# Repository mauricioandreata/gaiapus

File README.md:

# Gaiapus · Field Shift

**NASA Space Apps Challenge 2026** · Challenge *Field Shift: Adapting Farms with NASA Data* · Team Gaiapus

Gaiapus helps farmers decide **what to plant next, and when**, without leaving the soil bare between one crop and the next. Recommendations start from open NASA data, which covers any place on the planet. Where local precision matters, a **low-cost solar soil stake** measures the field and corrects the satellite data for that spot.

> The tool suggests and explains; the final decision always belongs to the farmer and the local agronomist.

| 3D model of the stake (real design, generated from the boards and the case) | Product concept (illustrative image, **AI-generated**) |
|---|---|
|  |  |

*Portuguese version: [`README.pt-BR.md`](README.pt-BR.md).*

---

## The problem

- Satellite data is the only source available to most farmers, but it is **too coarse to decide on a single field**: SMAP soil moisture comes in 9 km cells, GPM IMERG rainfall in ~10 km cells, and no satellite measures soil temperature at 15 or 40 cm.
- Commercial soil sensors cost **hundreds of dollars per depth**, plus a datalogger. They are out of reach for the farmers who most need guidance.
- Worldwide, more than 500 million family farms produce about 80 % of the world's food by value (FAO), and agriculture accounts for about 72 % of all freshwater withdrawals (FAO, AQUASTAT 2025).
- **(Brazil, pilot region)** 77 % of rural establishments are family farms and only about 20 % receive technical assistance (IBGE, Agricultural Census 2017).

## The solution in three tiers

| Tier | For whom | What goes to the field | How the farmer receives it |
|---|---|---|---|
| **0 · Satellite** | any farmer, zero cost | nothing, just the location | app and WhatsApp (voice and text) |
| **1 · Stake** | small farms | 1 solar stake + 1 community gateway (cooperative, extension service) | WhatsApp + green/yellow/red LEDs on the stake |
| **2 · Network** | medium and large farms | several stakes per management zone | app, per field |

```mermaid
flowchart LR
    NASA["NASA data<br/>POWER · GPM IMERG · SMAP<br/>HLS · SRTM"] --> M["Decision engine<br/>rotation and planting window"]
    E["Gaiapus stake<br/>soil moisture and temp. 15/40 cm<br/>air · rain"] -- "LoRa" --> G["Community<br/>gateway"]
    G -- "Wi-Fi / MQTT" --> M
    M --> P["Farmer<br/>WhatsApp · app · stake LEDs"]
```

---

## What is in this repository

This repository contains the **device**: hardware, firmware and mechanics. The app and the decision engine with the NASA data live in the software team's repository. The two connect through the data contract in [`docs/protocolo-dados.md`](docs/protocolo-dados.md) (Portuguese).

### Current status
| Part | Status | Evidence |
|---|---|---|
| Schematics of both boards (head + probe) | complete, ERC with no errors | `hardware/gaiapus-node`, `hardware/gaiapus-probe` |
| Head PCB (90 × 50 mm, 4 layers) | routed 51/51 nets, DRC with no errors | `hardware/gaiapus-node/*.kicad_pcb`, 3D model `.glb`/`.step` |
| Probe PCB (22 × 450 mm, 2 layers) | routed 12/12 nets, DRC with no errors | `hardware/gaiapus-probe/*.kicad_pcb` |
| Bill of materials with cost | every main part with LCSC code and price | `bom/bom_custos_BRL.xlsx` |
| Power budget | computed from datasheet values | `power/power_budget.py` |
| Case, stake and rain gauge (rev G) | drawings, printable 3MF files, full 3D assembly, 36/36 checks passed, 0 mm³ interference | `mechanical/` |
| Stake and gateway firmware | complete, tested on a PC (9 simulated hours, network outage, resend) | `firmware/` |
| Bench prototype | dev-board ESP32 + off-the-shelf sensors, same firmware and protocol | `firmware/src/main.cpp` |
| Physical PCB prototype | **not manufactured yet** | — |

### Key numbers
| | Value |
|---|---|
| Measurements | soil moisture and temperature at 15 and 40 cm, air temperature and humidity, rainfall, battery |
| Radio | LoRa (SX1262), configurable regional band 868/915 MHz; 25 bytes every 30 min |
| Consumption | 1.2–1.8 mAh/day (50–75 µA average) |
| Energy | 0.3 W panel (68 × 37 mm) + LiFePO4 18650 cell; positive balance even on a cloudy day |
| Autonomy without sun | about 1 year by calculation (target was 14 days) |
| Rain gauge | tipping bucket, 100 mm collector, 0.201 mm per pulse |
| Component cost | ≈ US$ 30 per stake (1 unit), less in volume; PCB, assembly and case still to be quoted |
| Comparison | a commercial single-depth sensor costs US$ 258–615, without the logger |

Details, sources and limits of each number: [`docs/hardware.md`](docs/hardware.md).

---

## Where to start

### Judges and reviewers
1. [`docs/hardware.md`](docs/hardware.md): why each component, power, cost, market comparison, risks.
2. [`docs/firmware.md`](docs/firmware.md): how the stake measures, stores and sends data all the way to the app.
3. [`docs/protocolo-dados.md`](docs/protocolo-dados.md) (Portuguese): the 25-byte packet and the JSON the app receives.
4. 3D model of the whole stake: [`mechanical/cad/revG/gaiapus-stake-revG-assembly.glb`](mechanical/cad/revG/gaiapus-stake-revG-assembly.glb) (opens in Windows 3D Viewer, Blender or https://gltf-viewer.donmccurdy.com).
5. Case and rain-gauge drawings: [`mechanical/drawings/gaiapus-case-revG.pdf`](mechanical/drawings/gaiapus-case-revG.pdf); exploded view: [`mechanical/cad/revG/renders/exploded-revG.png`](mechanical/cad/revG/renders/exploded-revG.png).
6. Design decisions and their reasons: [`docs/decisoes.md`](docs/decisoes.md) (Portuguese).

### Team
| I want to... | Do |
|---|---|
| Open the boards | KiCad 8: `hardware/gaiapus-node/gaiapus-node.kicad_pro` and `hardware/gaiapus-probe/gaiapus-probe.kicad_pro` |
| Change the circuit | edit `hardware/tools/gen_kicad.py` and run `check_kicad.py` (see [`hardware/README.md`](hardware/README.md)); close KiCad first |
| Flash the stake | `cd firmware && pio run -e stake-lora -t upload` (other targets in [`firmware/README.md`](firmware/README.md)) |
| Run the firmware tests | in `firmware/test`, commands in [`firmware/README.md`](firmware/README.md) (needs only `gcc` and `python3`) |
| Recompute the energy budget | `python power/power_budget.py --help` |
| Integrate the app | subscribe to `gaiapus/devices/+/up` and publish the command to `gaiapus/devices/{id}/down` ([`docs/protocolo-dados.md`](docs/protocolo-dados.md)) |

---

## Structure

| Folder | Contents |
|---|---|
| `docs/` | documentation: hardware, firmware, protocol, requirements, decisions |
| `hardware/gaiapus-node/` | head board (KiCad 8): ESP32-S3, LoRa radio, solar power, air sensor, LEDs, USB-C |
| `hardware/gaiapus-probe/` | probe board (KiCad 8): moisture electrodes and temperature sensors inside the tube |
| `hardware/lib/` | symbols, footprints and 3D models |
| `hardware/datasheets/` | datasheet of every main component |
| `hardware/tools/` | board generation, placement, routing and verification scripts |
| `bom/` | bill of materials and costs |
| `power/` | power budget |
| `firmware/` | stake, gateway and bench firmware, with tests |
| `mechanical/` | case, stake, rain gauge, drawings, printable parts and 3D assembly |
| `renders/` | concept images (AI-generated) |

---

## Declared limits

- The PCB **has not been manufactured yet**. Power, radio range and sensor readings come from datasheets, calculation and simulation, not from measurement.
- Measuring moisture **through the tube wall** is an assumption to be tested in real soil. If the wall attenuates too much, plan B is to open windows in the tube without changing the board.
- The stake measures to **decide** (irrigate, plant, wait), not for research: it needs per-probe calibration (air and water) and per-soil-type calibration.
- The price quoted is for **components**, not a retail price.
- Data marked **(Brazil)** comes from the pilot in Uberlândia (MG). The hardware and the method apply to any region.

## NASA data and other sources

- **NASA:** POWER (temperature, solar radiation; also used to size the solar panel), GPM IMERG (rainfall), SMAP L4 (soil moisture), HLS (vegetation, bare soil), SRTM (elevation, slope).
- **Other:** ZARC agricultural climate-risk zoning (MAPA, Brazil), SoilGrids (ISRIC), IBGE Agricultural Census 2017, FAO, ANA.
- **Tools and libraries:** KiCad 8, PlatformIO/Arduino, RadioLib, PubSubClient, DHTesp, LCSC/JLCPCB part library and 3D models, component datasheets in `hardware/datasheets/`.

## AI assistance

In line with the NASA Space Apps rules on Super Intelligence (SI) tools:

- **Images:** `renders/design-base-v1.jpg` is an **AI-generated** concept image, used only as a style reference. All other renders and drawings are generated from our own CAD and KiCad models.
- **Code:** parts of the firmware and of the Python tooling (board generation, routing and verification, mechanical CAD and drawings, power budget) were written with the help of an AI assistant (Claude, by Anthropic) and reviewed, tested and integrated by the team.
- **Text:** documentation drafts and translations were produced with AI assistance and reviewed by the team.

No NASA logos or branding are used in this project.

## Hardware design rules (for the team)

1. Everything SMD soldered directly to the board, with certified modules for radio and MCU. No pin headers, sockets or development boards.
2. Every component with footprint, 3D model, datasheet and LCSC code (cost and assembly at JLCPCB).
3. Every relevant choice goes into [`docs/decisoes.md`](docs/decisoes.md) with its reason.
4. Data from a specific country is always marked as such.

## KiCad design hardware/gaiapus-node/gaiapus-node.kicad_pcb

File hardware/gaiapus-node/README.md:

# gaiapus-node (KiCad 8)

Schematic is hierarchical, 5 sheets joined by global labels and power symbols (no sheet pins):

| Sheet | File | Content |
|---|---|---|
| Power | `power.kicad_sch` | solar input + zener, CN3058E charger, 18650 holder, HY2112 + FS8205A, TPS63802 3.3 V, battery divider |
| MCU | `mcu.kicad_sch` | ESP32-S3-MINI-1-N8, reset/boot, decoupling, UART test pads |
| LoRa | `lora.kicad_sch` | E22-900MM22S, ANT pad -> 0R -> U.FL |
| Sensors | `sensors.kicad_sch` | 2 x moisture oscillators + electrodes, 2 x NTC, SHT40, rain input |
| Interface | `interface.kicad_sch` | USB-C + ESD, 3 LEDs |

## How these files were made
`python3 hardware/tools/gen_kicad.py` writes the schematic, the symbol library (`../lib/symbols/gaiapus.kicad_sym`), `netlist-draft.csv` and `bom/bom_from_schematic.csv`.
`python3 hardware/tools/check_kicad.py` re-derives connectivity from the raw geometry and compares it with the intended nets (must print `RESULT: OK`).
Pin numbers come from the vendor datasheets (see `docs/component-selection.md`, `docs/hardware-pinmap.md`).

**Rule:** either edit the script and regenerate, or edit in KiCad and stop regenerating (regeneration overwrites the sheets). Close KiCad before regenerating.

## First steps in KiCad
1. Close KiCad (lock files `~*.lck` are from an old session), reopen `gaiapus-node.kicad_pro`.
2. Inspection > Electrical Rules Checker. Send the report back; expected leftovers are pin-type warnings, not missing connections.
3. Tools > Assign Footprints; draw the custom ones (list in `docs/hardware-pinmap.md`).
4. Tools > Update PCB from Schematic.

Symbol fields on every part: Value, Footprint, LCSC, MPN, Manufacturer, Note (hidden).

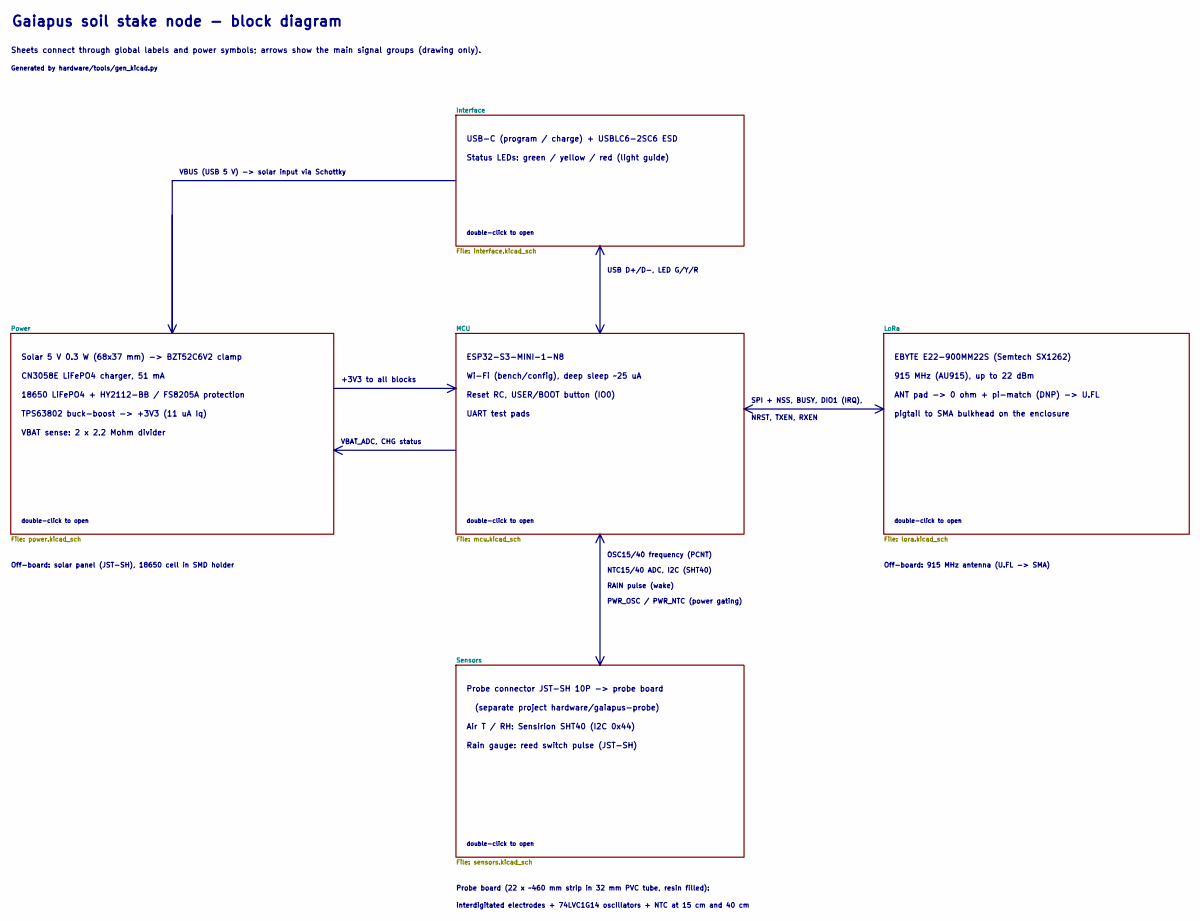
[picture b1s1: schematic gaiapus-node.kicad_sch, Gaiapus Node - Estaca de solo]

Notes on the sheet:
double-click to open
USB-C (program / charge) + USBLC6-2SC6 ESD
TPS63802 buck-boost -> +3V3 (11 uA Iq)
Reset RC, USER/BOOT button (IO0)
Air T / RH: Sensirion SHT40 (I2C 0x44)
Probe connector JST-SH 10P -> probe board
Off-board: solar panel (JST-SH), 18650 cell in SMD holder
ANT pad -> 0 ohm + pi-match (DNP) -> U.FL
Wi-Fi (bench/config), deep sleep ~25 uA
OSC15/40 frequency (PCNT)
ESP32-S3-MINI-1-N8
VBAT sense: 2 x 2.2 Mohm divider
NRST, TXEN, RXEN
Probe board (22 x ~460 mm strip in 32 mm PVC tube, resin filled):
PWR_OSC / PWR_NTC (power gating)
CN3058E LiFePO4 charger, 51 mA
Rain gauge: reed switch pulse (JST-SH)
VBUS (USB 5 V) -> solar input via Schottky
VBAT_ADC, CHG status
(separate project hardware/gaiapus-probe)
interdigitated electrodes + 74LVC1G14 oscillators + NTC at 15 cm and 40 cm
18650 LiFePO4 + HY2112-BB / FS8205A protection
UART test pads
USB D+/D-, LED G/Y/R
Sheets connect through global labels and power symbols; arrows show the main signal groups (drawing only).
Status LEDs: green / yellow / red (light guide)
EBYTE E22-900MM22S (Semtech SX1262)
SPI + NSS, BUSY, DIO1 (IRQ),
Off-board: 915 MHz antenna (U.FL -> SMA)
915 MHz (AU915), up to 22 dBm
Generated by hardware/tools/gen_kicad.py
NTC15/40 ADC, I2C (SHT40)
Solar 5 V 0.3 W (68x37 mm) -> BZT52C6V2 clamp
Gaiapus soil stake node - block diagram
+3V3 to all blocks
RAIN pulse (wake)
pigtail to SMA bulkhead on the enclosure

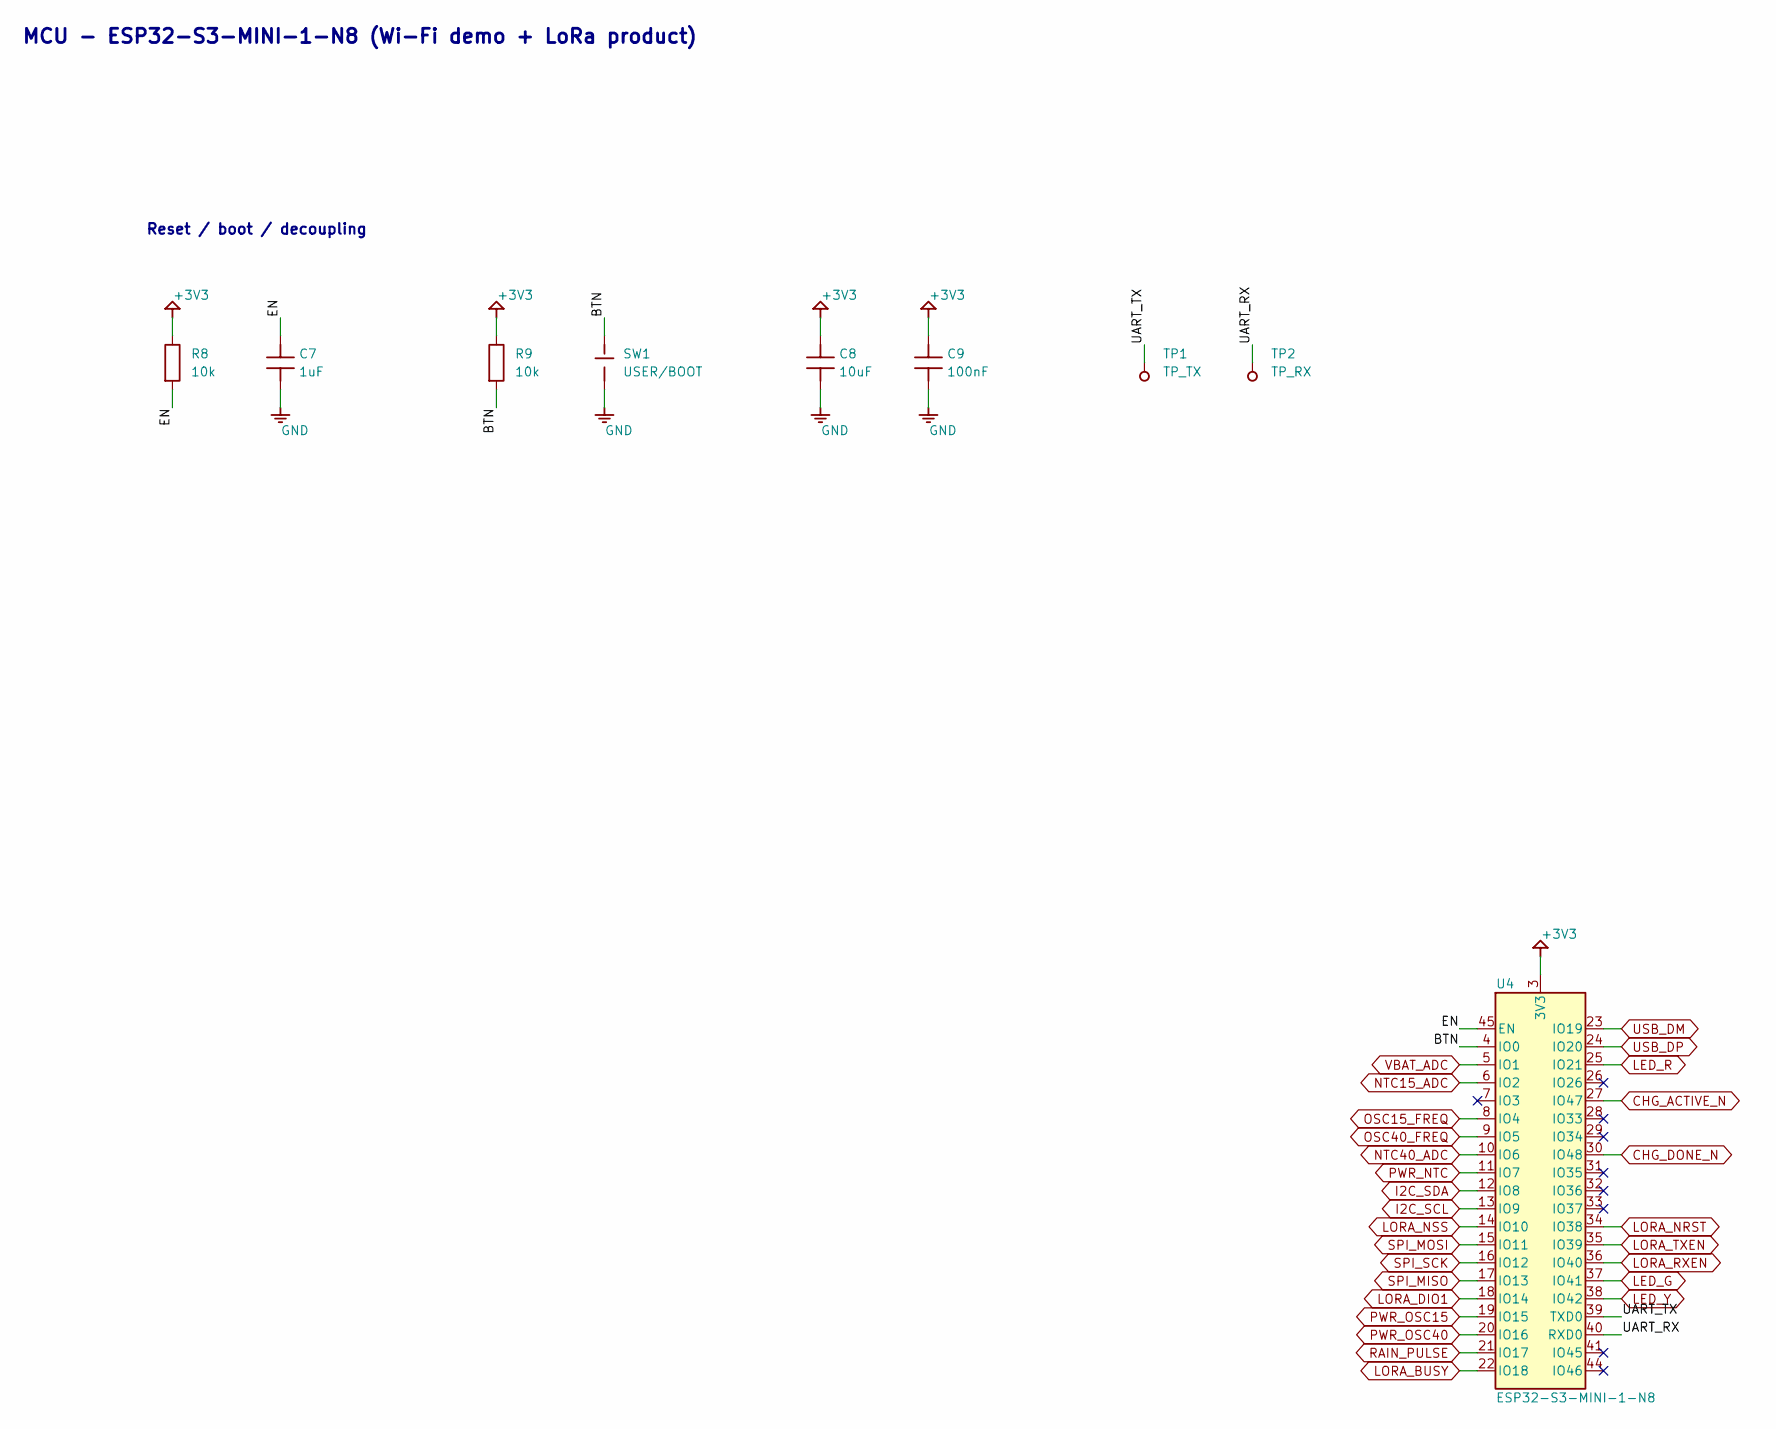
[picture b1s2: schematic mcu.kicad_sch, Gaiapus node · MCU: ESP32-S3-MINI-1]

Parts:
C7: 1uF; C_0603_1608Metric; LCSC TBD
C8: 10uF; C_0805_2012Metric; LCSC TBD
C9: 100nF; C_0603_1608Metric; LCSC TBD
R8, R9: 10k; R_0603_1608Metric; LCSC TBD
SW1: USER/BOOT; SW_SPST_PTS810; LCSC TBD
TP1: TP_TX; TestPoint_Pad_D1.5mm; LCSC TBD
TP2: TP_RX; TestPoint_Pad_D1.5mm; LCSC TBD
U4: ESP32-S3-MINI-1-N8; BULETM-SMD_ESP32-S3-MINI-1-N8; MPN ESP32-S3-MINI-1-N8; LCSC C2913206

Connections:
+3V3: C8.1, C9.1, R8.1, R9.1, U4.3 (3V3); also elsewhere on the board
/MCU/BTN: R9.2, SW1.1, U4.4 (IO0)
/MCU/EN: C7.1, R8.2, U4.45 (EN)
/MCU/UART_RX: TP2.1 (TP), U4.40 (RXD0)
/MCU/UART_TX: TP1.1 (TP), U4.39 (TXD0)
CHG_ACTIVE_N: U4.27 (IO47); also elsewhere on the board
CHG_DONE_N: U4.30 (IO48); also elsewhere on the board
I2C_SCL: U4.13 (IO9); also elsewhere on the board
I2C_SDA: U4.12 (IO8); also elsewhere on the board
LED_G: U4.37 (IO41); also elsewhere on the board
LED_R: U4.25 (IO21); also elsewhere on the board
LED_Y: U4.38 (IO42); also elsewhere on the board
LORA_BUSY: U4.22 (IO18); also elsewhere on the board
LORA_DIO1: U4.18 (IO14); also elsewhere on the board
LORA_NRST: U4.34 (IO38); also elsewhere on the board
LORA_NSS: U4.14 (IO10); also elsewhere on the board
LORA_RXEN: U4.36 (IO40); also elsewhere on the board
LORA_TXEN: U4.35 (IO39); also elsewhere on the board
NTC15_ADC: U4.6 (IO2); also elsewhere on the board
NTC40_ADC: U4.10 (IO6); also elsewhere on the board
OSC15_FREQ: U4.8 (IO4); also elsewhere on the board
OSC40_FREQ: U4.9 (IO5); also elsewhere on the board
PWR_NTC: U4.11 (IO7); also elsewhere on the board
PWR_OSC15: U4.19 (IO15); also elsewhere on the board
PWR_OSC40: U4.20 (IO16); also elsewhere on the board
RAIN_PULSE: U4.21 (IO17); also elsewhere on the board
SPI_MISO: U4.17 (IO13); also elsewhere on the board
SPI_MOSI: U4.15 (IO11); also elsewhere on the board
SPI_SCK: U4.16 (IO12); also elsewhere on the board
USB_DM: U4.23 (IO19); also elsewhere on the board
USB_DP: U4.24 (IO20); also elsewhere on the board
VBAT_ADC: U4.5 (IO1); also elsewhere on the board

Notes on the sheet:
MCU - ESP32-S3-MINI-1-N8 (Wi-Fi demo + LoRa product)
Reset / boot / decoupling

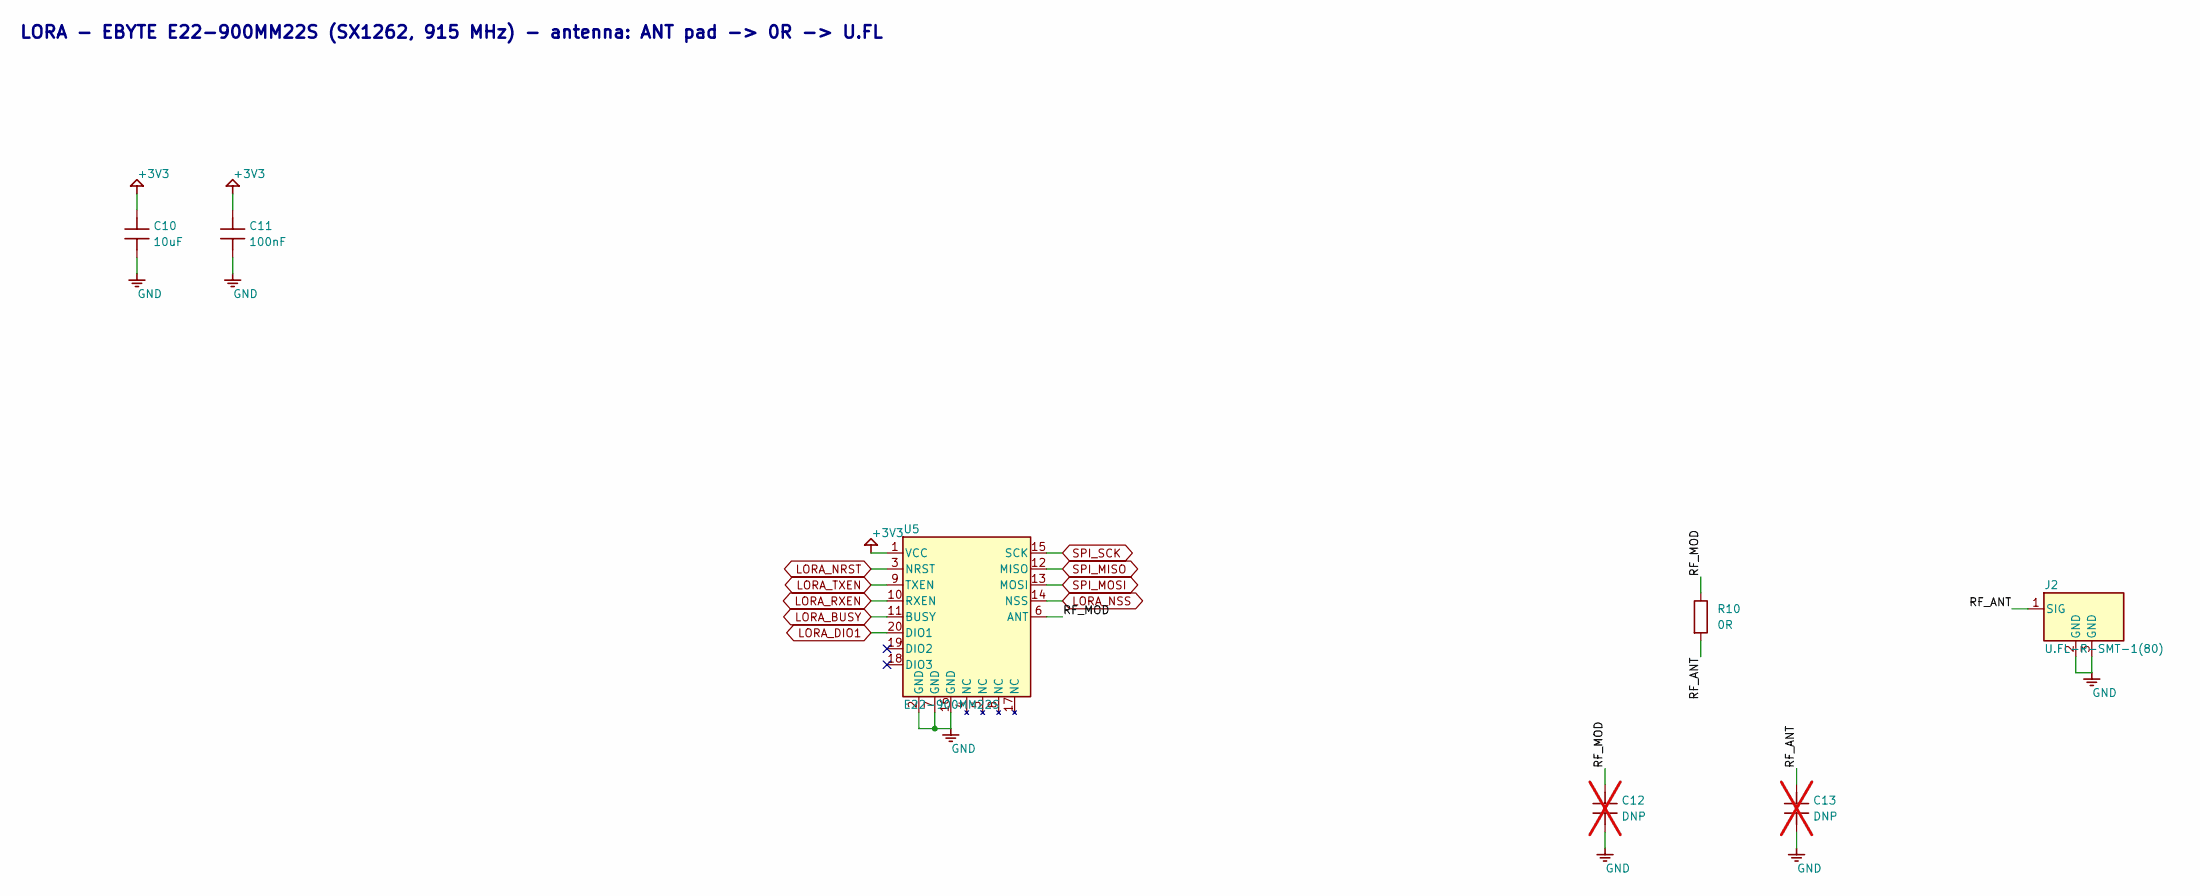
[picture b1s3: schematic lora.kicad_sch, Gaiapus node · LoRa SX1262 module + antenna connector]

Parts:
C10: 10uF; C_0805_2012Metric; LCSC TBD
C11: 100nF; C_0603_1608Metric; LCSC TBD
C12, C13: DNP; C_0603_1608Metric; LCSC TBD; not fitted
J2: U.FL-R-SMT-1(80); RF-SMD_FRF05002-JSS103M; MPN U.FL-R-SMT-1(80); LCSC C88374
R10: 0R; R_0603_1608Metric; LCSC TBD
U5: E22-900MM22S; WIRELM-SMD_20P-L10.0-W10.0-P1.27-TL; MPN E22-900MM22S; LCSC C5333985

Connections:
+3V3: C10.1, C11.1, U5.1 (VCC); also elsewhere on the board
/LoRa/RF_ANT: C13.1, J2.1 (SIG), R10.2
/LoRa/RF_MOD: C12.1, R10.1, U5.6 (ANT)
LORA_BUSY: U5.11 (BUSY); also elsewhere on the board
LORA_DIO1: U5.20 (DIO1); also elsewhere on the board
LORA_NRST: U5.3 (NRST); also elsewhere on the board
LORA_NSS: U5.14 (NSS); also elsewhere on the board
LORA_RXEN: U5.10 (RXEN); also elsewhere on the board
LORA_TXEN: U5.9 (TXEN); also elsewhere on the board
SPI_MISO: U5.12 (MISO); also elsewhere on the board
SPI_MOSI: U5.13 (MOSI); also elsewhere on the board
SPI_SCK: U5.15 (SCK); also elsewhere on the board

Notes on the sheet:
LORA - EBYTE E22-900MM22S (SX1262, 915 MHz) - antenna: ANT pad -> 0R -> U.FL

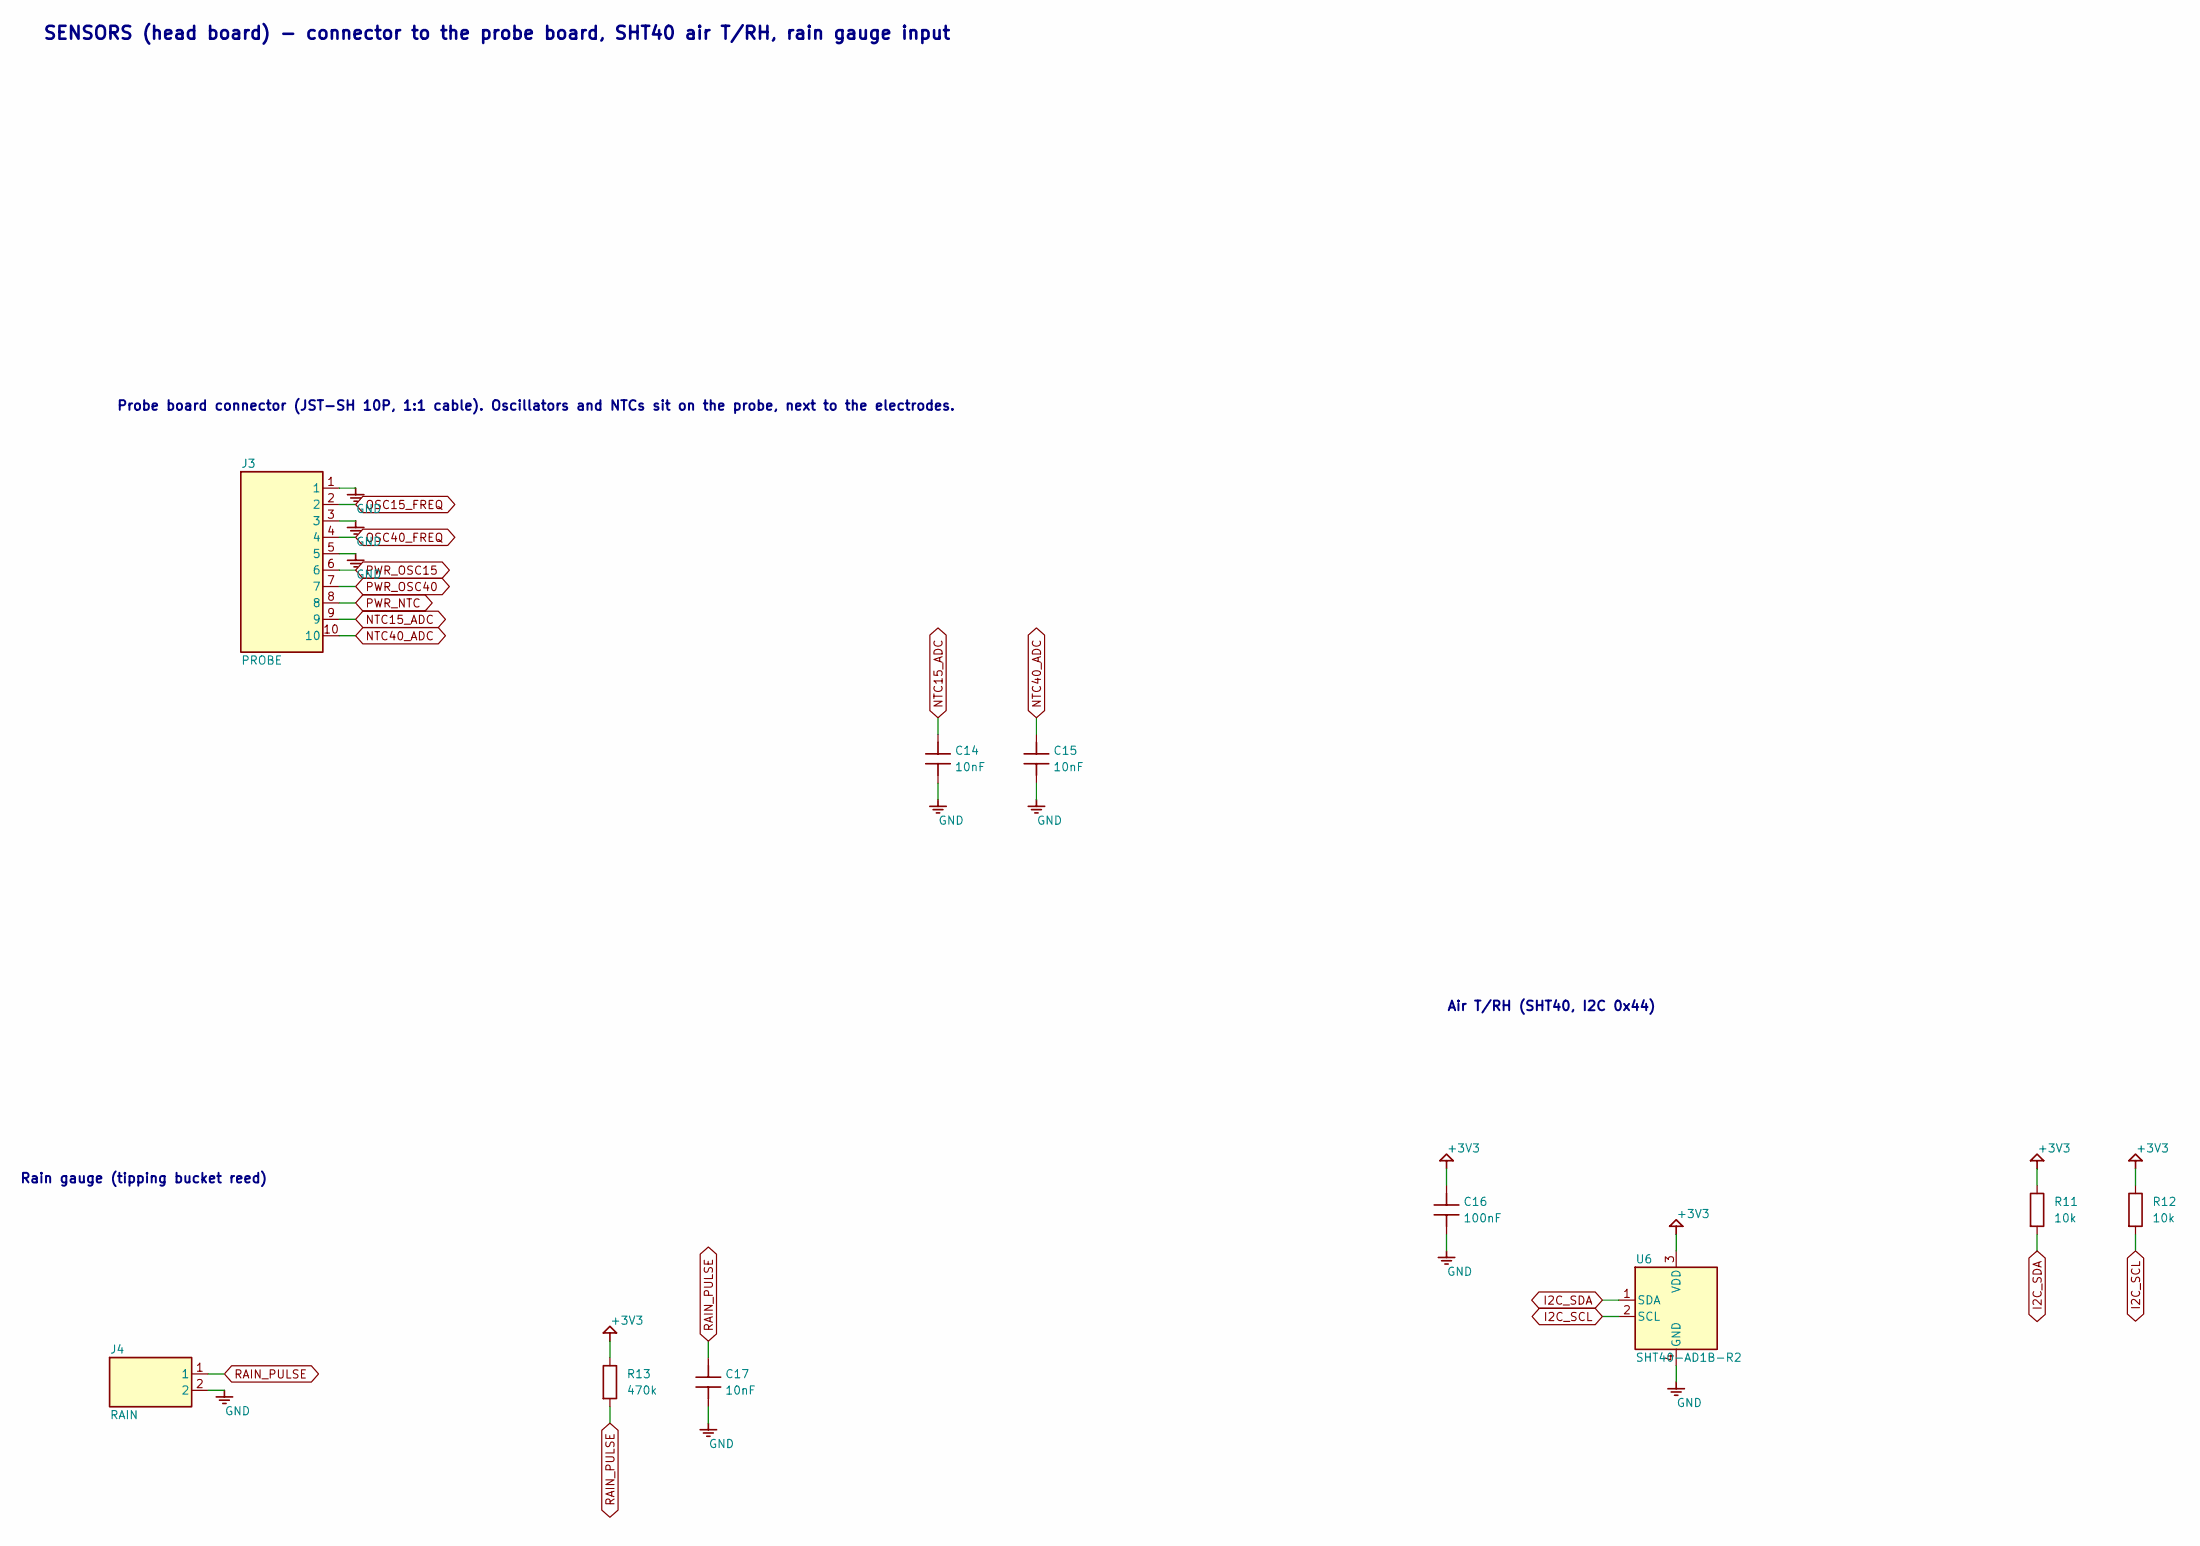
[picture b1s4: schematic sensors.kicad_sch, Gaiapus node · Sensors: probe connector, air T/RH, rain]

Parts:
C14, C15, C17: 10nF; C_0603_1608Metric; LCSC TBD
C16: 100nF; C_0603_1608Metric; LCSC TBD
J3: PROBE; CONN-SMD_10P-P1.00_SM10B-SRSS-TB-LF-SN; MPN SM10B-SRSS-TB(LF)(SN); LCSC C160409
J4: RAIN; JST_SH_SM02B-SRSS-TB_1x02-1MP_P1.00mm_Horizontal; MPN SM02B-SRSS-TB; LCSC TBD
R11, R12: 10k; R_0603_1608Metric; LCSC TBD
R13: 470k; R_0603_1608Metric; LCSC TBD
U6: SHT40-AD1B-R2; DFN-4_L1.5-W1.5-P0.8-TL-EP; MPN SHT40-AD1B-R2; LCSC C2909890

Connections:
+3V3: C16.1, R11.1, R12.1, R13.1, U6.3 (VDD); also elsewhere on the board
I2C_SCL: R12.2, U6.2 (SCL); also elsewhere on the board
I2C_SDA: R11.2, U6.1 (SDA); also elsewhere on the board
NTC15_ADC: C14.1, J3.9; also elsewhere on the board
NTC40_ADC: C15.1, J3.10; also elsewhere on the board
OSC15_FREQ: J3.2; also elsewhere on the board
OSC40_FREQ: J3.4; also elsewhere on the board
PWR_NTC: J3.8; also elsewhere on the board
PWR_OSC15: J3.6; also elsewhere on the board
PWR_OSC40: J3.7; also elsewhere on the board
RAIN_PULSE: C17.1, J4.1, R13.2; also elsewhere on the board

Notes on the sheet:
Rain gauge (tipping bucket reed)
Air T/RH (SHT40, I2C 0x44)
Probe board connector (JST-SH 10P, 1:1 cable). Oscillators and NTCs sit on the probe, next to the electrodes.
SENSORS (head board) - connector to the probe board, SHT40 air T/RH, rain gauge input

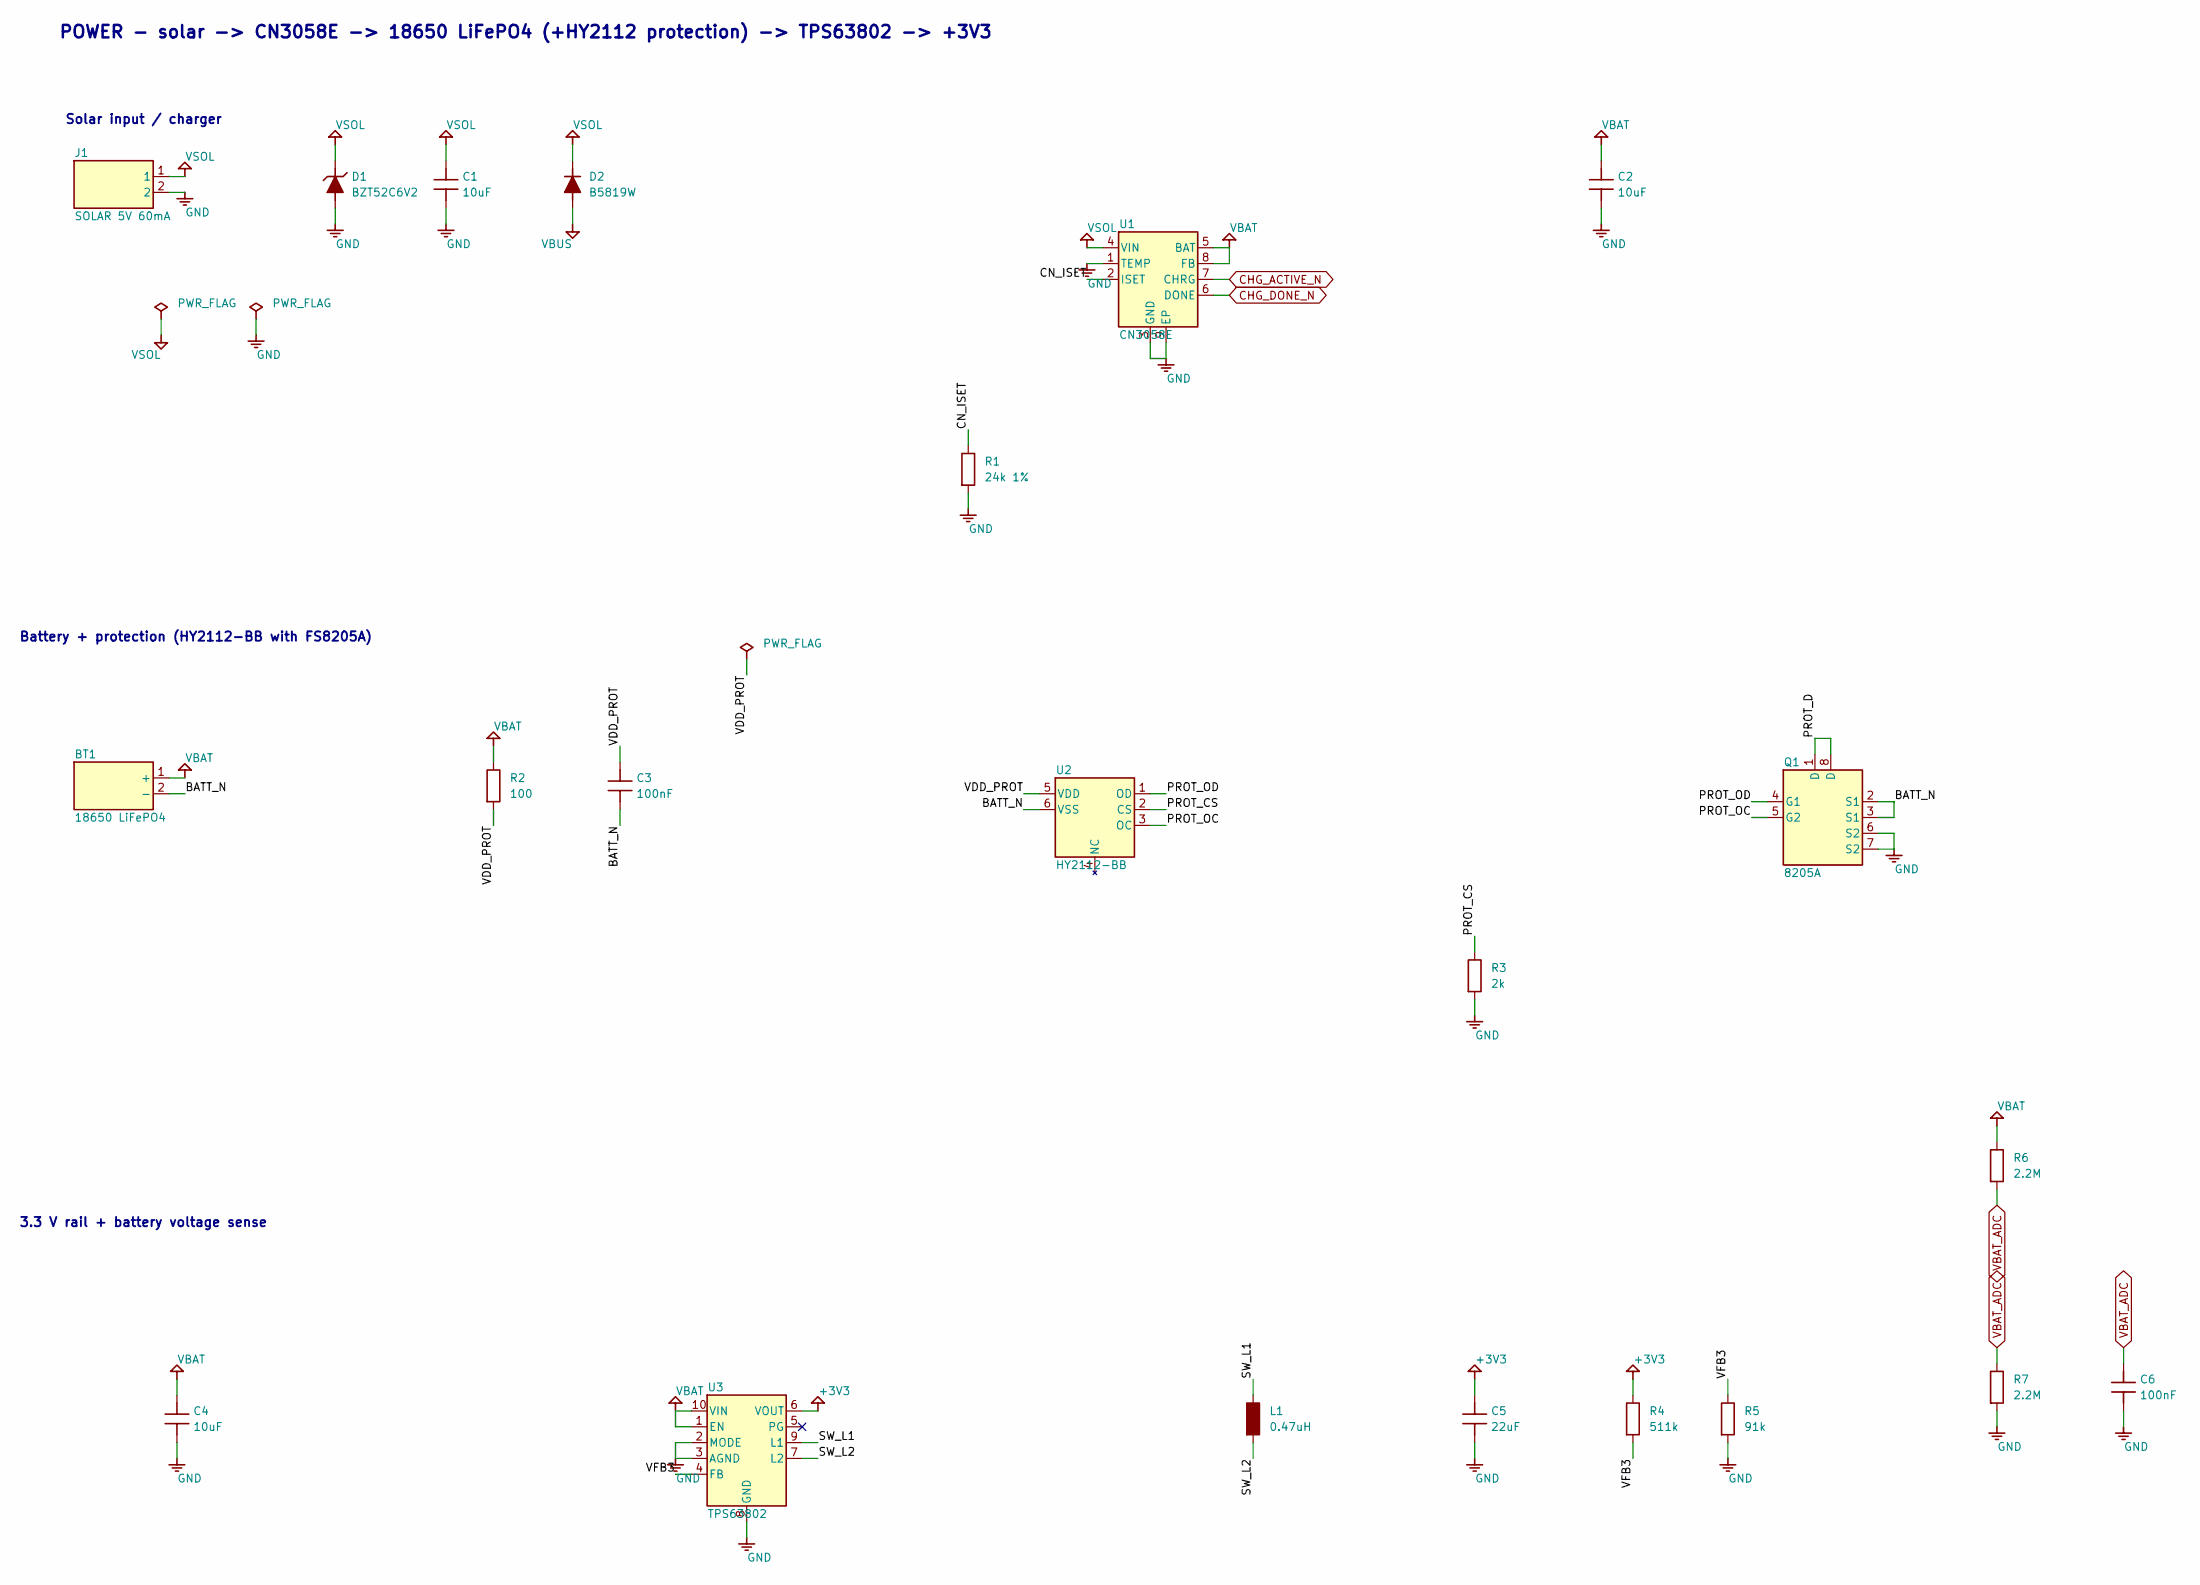
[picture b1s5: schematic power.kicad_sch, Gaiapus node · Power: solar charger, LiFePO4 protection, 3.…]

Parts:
BT1: 18650 LiFePO4; BATTERY-SMD_18650-1S-L77.1-W20.7-1; MPN BH-18650-B1BA002; LCSC C2988620
C1, C2, C4: 10uF; C_0805_2012Metric; LCSC TBD
C3, C6: 100nF; C_0603_1608Metric; LCSC TBD
C5: 22uF; C_0805_2012Metric; LCSC TBD
D1: BZT52C6V2; D_SOD-123; MPN BZT52C6V2; LCSC TBD
D2: B5819W; D_SOD-123; LCSC TBD
J1: SOLAR 5V 60mA; JST_SH_SM02B-SRSS-TB_1x02-1MP_P1.00mm_Horizontal; MPN SM02B-SRSS-TB; LCSC TBD
L1: 0.47uH; L_Taiyo-Yuden_NR-40xx; LCSC TBD
Q1: 8205A; TSSOP-8_L4.4-W3.0-P0.65-LS6.4-BL; MPN 8205A; LCSC C5148694
R1: 24k 1%; R_0603_1608Metric; LCSC TBD
R2: 100; R_0603_1608Metric; LCSC TBD
R3: 2k; R_0603_1608Metric; LCSC TBD
R4: 511k; R_0603_1608Metric; LCSC TBD
R5: 91k; R_0603_1608Metric; LCSC TBD
R6, R7: 2.2M; R_0603_1608Metric; LCSC TBD
U1: CN3058E; SOIC-8_L4.9-W3.9-P1.27-LS6.0-BL-EP3.3; MPN CN3058E; LCSC C112011
U2: HY2112-BB; SOT-23-6_L2.9-W1.6-P0.95-LS2.8-BR; MPN HY2112-BB; LCSC C161942
U3: TPS63802; VSON-10_L3.0-W2.0-P0.50-TL; MPN TPS63802DLAR; LCSC C2845237

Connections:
+3V3: C5.1, R4.1, U3.6 (VOUT); also elsewhere on the board
/Power/BATT_N: BT1.2 (-), C3.2, Q1.2 (S1), Q1.3 (S1), U2.6 (VSS)
/Power/CN_ISET: R1.1, U1.2 (ISET)
/Power/PROT_CS: R3.1, U2.2 (CS)
/Power/PROT_D: Q1.1 (D), Q1.8 (D)
/Power/PROT_OC: Q1.5 (G2), U2.3 (OC)
/Power/PROT_OD: Q1.4 (G1), U2.1 (OD)
/Power/SW_L1: L1.1, U3.9 (L1)
/Power/SW_L2: L1.2, U3.7 (L2)
/Power/VDD_PROT: C3.1, R2.2, U2.5 (VDD)
/Power/VFB3: R4.2, R5.1, U3.4 (FB)
CHG_ACTIVE_N: U1.7 (CHRG); also elsewhere on the board
CHG_DONE_N: U1.6 (DONE); also elsewhere on the board
VBAT: BT1.1 (+), C2.1, C4.1, R2.1, R6.1, U1.5 (BAT), U1.8 (FB), U3.1 (EN), U3.10 (VIN)
VBAT_ADC: C6.1, R6.2, R7.1; also elsewhere on the board
VBUS: D2.2 (A); also elsewhere on the board
VSOL: C1.1, D1.1 (K), D2.1 (K), J1.1, U1.4 (VIN)

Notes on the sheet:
POWER - solar -> CN3058E -> 18650 LiFePO4 (+HY2112 protection) -> TPS63802 -> +3V3
Solar input / charger
3.3 V rail + battery voltage sense
Battery + protection (HY2112-BB with FS8205A)
